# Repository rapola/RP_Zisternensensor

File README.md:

# RP_Zisternensensor
Wasser-Füllstandsensor für Zisternen
 * ## Hauptplatine für Auswertung und MQTT Sender
 
  <br>
  
  * ## Level Sensor:
  
  <br>

  ---
    
### Schematic

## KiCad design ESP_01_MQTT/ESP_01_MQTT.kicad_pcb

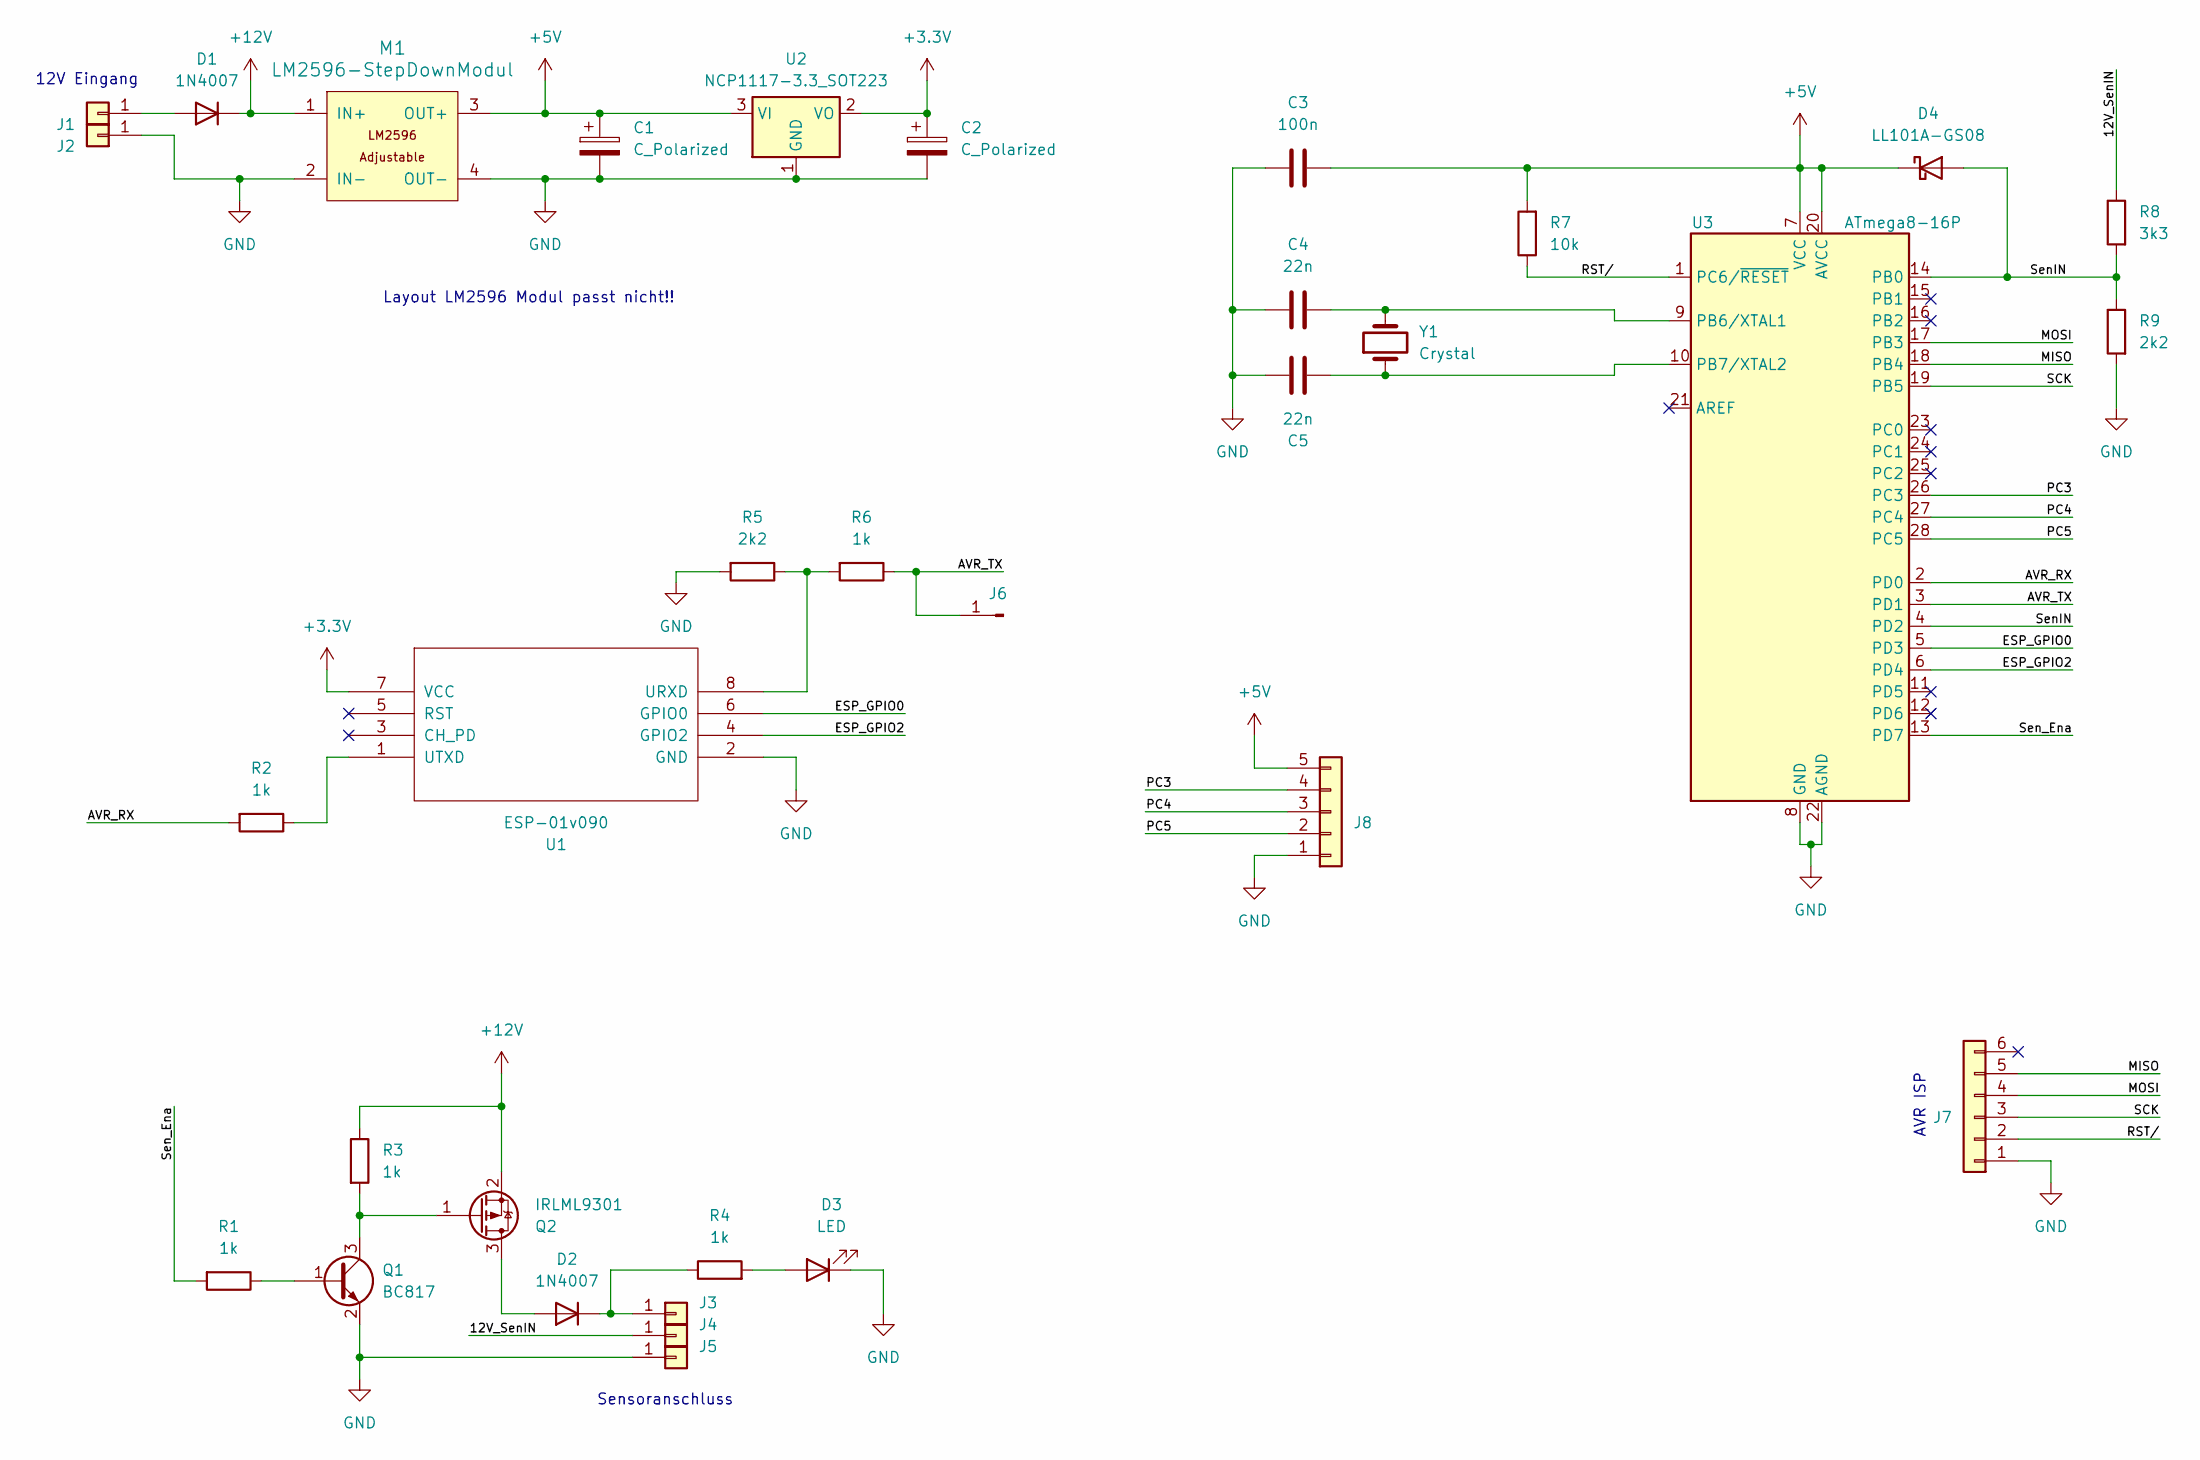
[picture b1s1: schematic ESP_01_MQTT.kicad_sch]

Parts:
C1, C2: C_Polarized; CP_Radial_D5.0mm_P2.00mm
C3: 100n; C_0805_2012Metric
C4, C5: 22n; C_0805_2012Metric
D1, D2: 1N4007; D_DO-41_SOD81_P10.16mm_Horizontal
D3: LED; LED_0805_2012Metric
D4: LL101A-GS08; D_MiniMELF
J1, J2, J3, J4, J5: Conn_01x01; Wago236-743_RM5
J6: Conn_01x01_Pin; PinHeader_1x01_P2.54mm_Vertical
J7: Conn_01x06; Molex_PicoBlade_53398-0671_1x06-1MP_P1.25mm_Vertical
J8: Conn_01x05; PinHeader_1x05_P2.54mm_Vertical
M1: LM2596-StepDownModul; YAAJ_DCDC_StepDown_LM2596_noSilk
Q1: BC817; SOT-23
Q2: IRLML9301; SOT-23
R1, R2, R3, R4, R6: 1k; R_0805_2012Metric
R5, R9: 2k2; R_0805_2012Metric
R7: 10k; R_0805_2012Metric
R8: 3k3; R_0805_2012Metric
U1: ESP-01v090; ESP-01
U2: NCP1117-3.3_SOT223; SOT-223-3_TabPin2
U3: ATmega8-16P; DIP-28_W7.62mm
Y1: Crystal; Crystal_HC49-4H_Vertical

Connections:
+3.3V: C2.1, U1.7 (VCC), U2.2 (VO)
+5V: C1.1, C3.2, D4.1 (K), J8.5, M1.3 (OUT+), R7.2, U2.3 (VI), U3.7 (VCC), U3.20 (AVCC)
+12V: D1.1 (K), M1.1 (IN+), Q2.2 (S), R3.1
/12V_SenIN: J4.1, R8.1
/AVR_RX: R2.2, U3.2 (PD0)
/AVR_TX: J6.1, R6.1, U3.3 (PD1)
/ESP_GPIO0: U1.6 (GPIO0), U3.5 (PD3)
/ESP_GPIO2: U1.4 (GPIO2), U3.6 (PD4)
/MISO: J7.5, U3.18 (PB4)
/MOSI: J7.4, U3.17 (PB3)
/PC3: J8.4, U3.26 (PC3)
/PC4: J8.3, U3.27 (PC4)
/PC5: J8.2, U3.28 (PC5)
/RST/: J7.2, R7.1, U3.1 (PC6/~RESET)
/SCK: J7.3, U3.19 (PB5)
/SenIN: D4.2 (A), R8.2, R9.1, U3.4 (PD2), U3.14 (PB0)
/Sen_Ena: R1.2, U3.13 (PD7)
GND: C1.2, C2.2, C3.1, C4.1, C5.1, D3.1 (K), J2.1, J5.1, J7.1, J8.1, M1.2 (IN-), M1.4 (OUT-), Q1.2 (E), R5.2, R9.2, U1.2 (GND), U2.1 (GND), U3.8 (GND), U3.22 (AGND)
unnamed: D1.2 (A), J1.1
unnamed: D2.2 (A), Q2.3 (D)
unnamed: D2.1 (K), J3.1, R4.1
unnamed: D3.2 (A), R4.2
unnamed: Q1.1 (B), R1.1
unnamed: Q1.3 (C), Q2.1 (G), R3.2
unnamed: R5.1, R6.2, U1.8 (URXD)
unnamed: R2.1, U1.1 (UTXD)
unnamed: C4.2, U3.9 (PB6/XTAL1), Y1.2
unnamed: C5.2, U3.10 (PB7/XTAL2), Y1.1

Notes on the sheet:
12V Eingang
Layout LM2596 Modul passt nicht!!
Sensoranschluss
AVR ISP

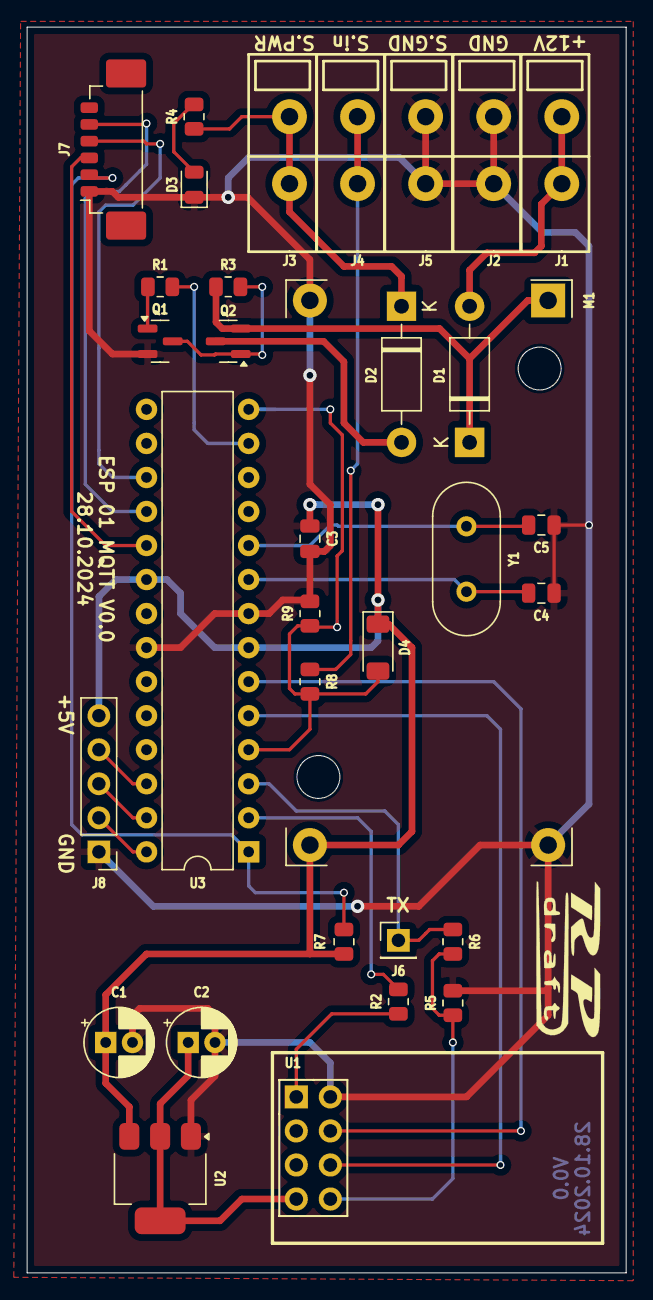
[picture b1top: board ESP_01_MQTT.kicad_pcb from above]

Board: 2 copper layers, 44.7 x 93.0 mm, 33 parts (0 on the bottom side), 28 nets.

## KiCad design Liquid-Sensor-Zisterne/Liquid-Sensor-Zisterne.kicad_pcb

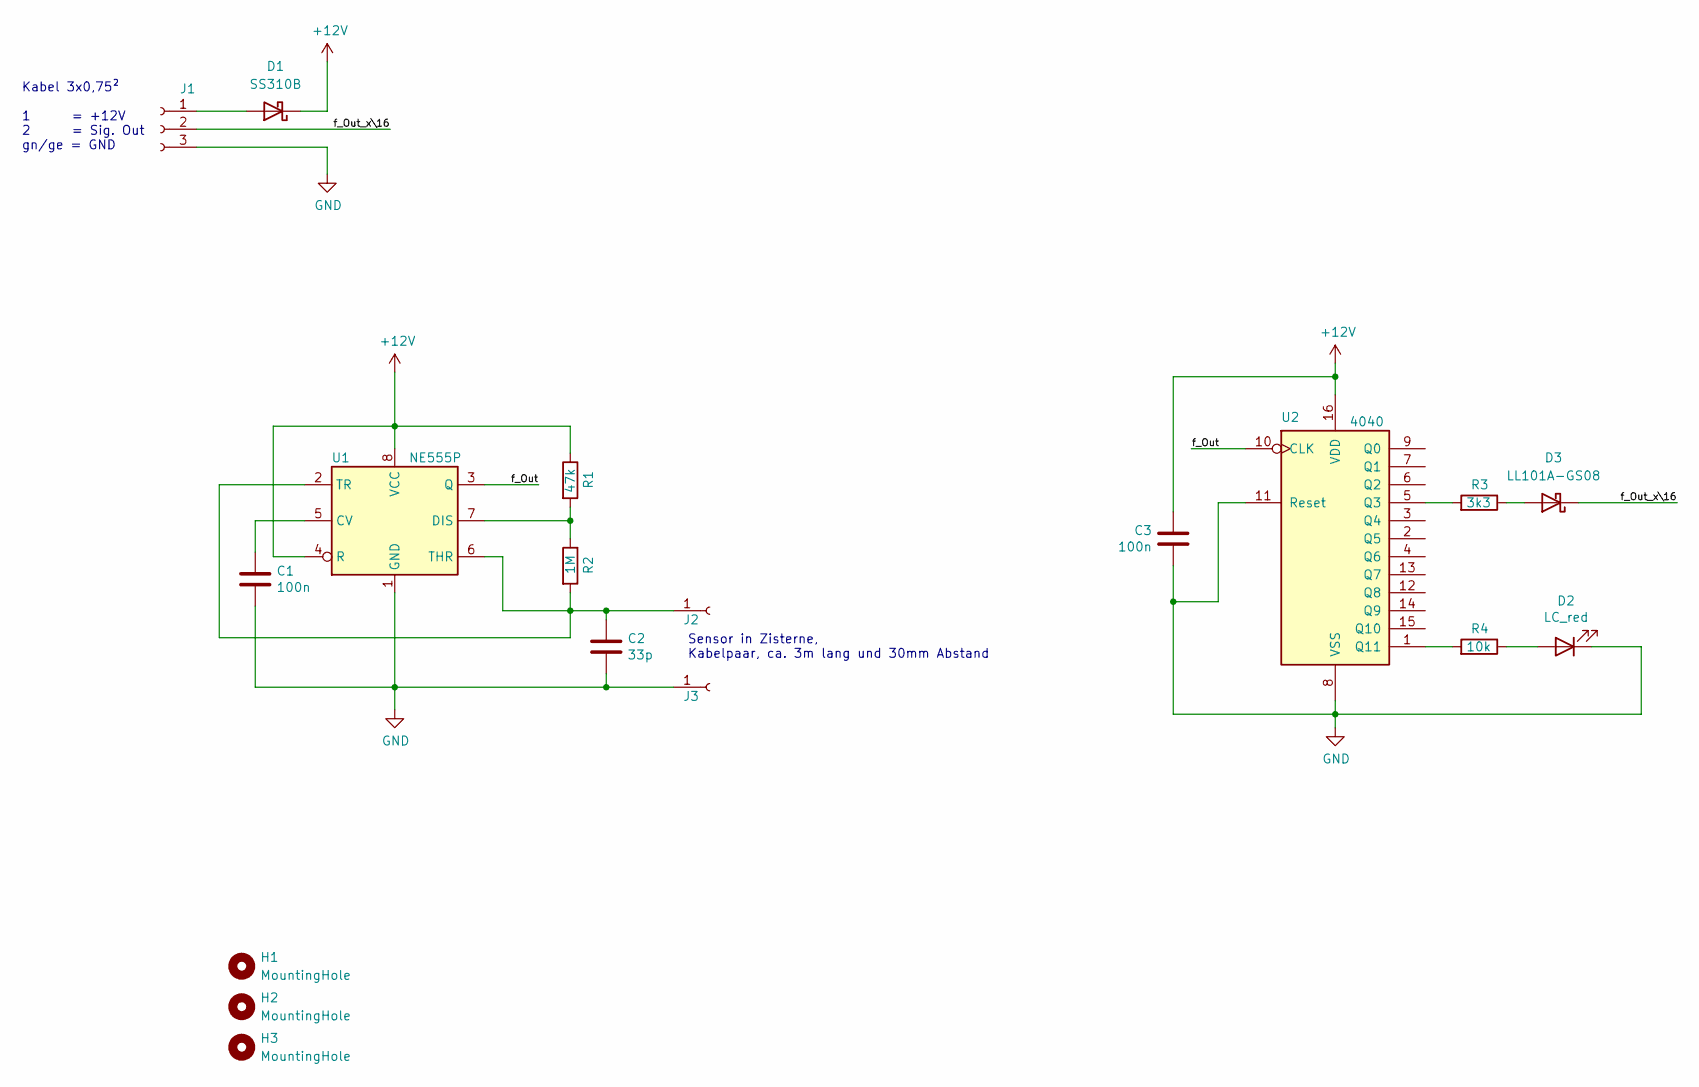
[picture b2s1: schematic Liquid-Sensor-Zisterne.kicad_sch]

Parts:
C1, C3: 100n; C_0805_2012Metric_Pad1.18x1.45mm_HandSolder
C2: 33p; C_Disc_D3.4mm_W2.1mm_P2.50mm
D1: SS310B; D_SMB_Handsoldering
D2: LC_red; LED_D3.0mm
D3: LL101A-GS08; D_MiniMELF
H1, H2, H3: MountingHole; MountingHole_3.2mm_M3_DIN965
J1: Conn_01x03_Female; PinHeader_1x03_P2.54mm_Horizontal
J2, J3: Conn_01x01_Female; TestPoint_Loop_D3.50mm_Drill1.4mm_Beaded
R1: 47k; R_0805_2012Metric_Pad1.20x1.40mm_HandSolder
R2: 1M; R_0805_2012Metric_Pad1.20x1.40mm_HandSolder
R3: 3k3; R_0805_2012Metric_Pad1.20x1.40mm_HandSolder
R4: 10k; R_0805_2012Metric_Pad1.20x1.40mm_HandSolder
U1: NE555P; SO-8_3.9x4.9mm_P1.27mm
U2: 4040; SOIC-16_3.9x9.9mm_P1.27mm

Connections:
+12V: C3.2, D1.1 (K), R1.1, U1.4 (R), U1.8 (VCC), U2.16 (VDD)
/f_Out: U1.3 (Q), U2.10 (CLK)
/f_Out_x\16: D3.1 (K), J1.2
GND: C1.2, C2.1, C3.1, D2.1 (K), J1.3, J3.1, U1.1 (GND), U2.8 (VSS), U2.11 (Reset)
unnamed: D1.2 (A), J1.1
unnamed: D2.2 (A), R4.1
unnamed: D3.2 (A), R3.1
unnamed: C2.2, J2.1, R2.2, U1.2 (TR), U1.6 (THR)
unnamed: C1.1, U1.5 (CV)
unnamed: R1.2, R2.1, U1.7 (DIS)
unnamed: R3.2, U2.5 (Q3)
unnamed: R4.2, U2.1 (Q11)

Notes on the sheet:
Sensor in Zisterne, Kabelpaar, ca. 3m lang und 30mm Abstand
Kabel 3x0,75² 1 = +12V 2 = Sig. Out gn/ge = GND

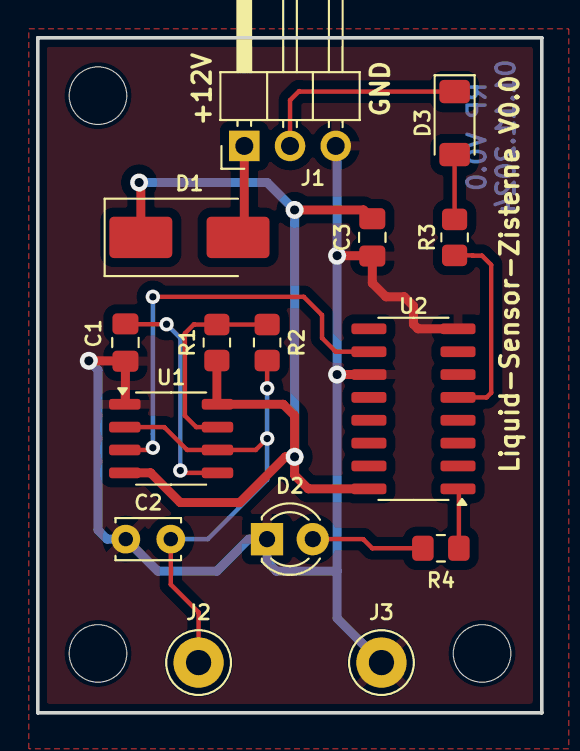
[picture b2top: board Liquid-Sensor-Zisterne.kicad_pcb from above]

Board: 2 copper layers, 28.0 x 37.5 mm, 18 parts (0 on the bottom side), 12 nets.

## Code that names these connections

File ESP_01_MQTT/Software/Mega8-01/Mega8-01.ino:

/*
Auswertung Freqeunzeingang
Arduino 1.8.19

AtMega8
PB0  AVR_ICP1          input from level-sensor
PD7  AVR_ENA_Sen12V    output, switch level-sensor on/off

- corresponding software: "ESP8266", always use same Vx.x !!
ToDo

*/

#include "src/RP_Arduino-SerialCommand/SerialCommand.h"	  		//Serial Command
#include <avr/interrupt.h> 

//-------------------------------------------------------
//global variables / constants
char SW_Vers[] = "Mega8-V1.0";

const uint8_t AVR_ICP1        = 8;                            //PB0;
const uint8_t AVR_ENA_Sen12V  = 7;                            //PD7;
const uint8_t PC_3            = 17;                           //not used, input pullup
const uint8_t PC_4            = 18;                           //not used, input pullup
const uint8_t PC_5            = 19;                           //not used, input pullup

const uint8_t AVR_ENA_Serial  = 3;                            //PD3; GPIO0 from ESP


struct tm{
  uint16_t capture_val;
  uint16_t ovf_val;
  uint16_t curr_capt_val;
  uint16_t curr_ovf_val;
};

volatile tm ICP;
uint32_t freq_timeout = 3000;                                 //3s timeout
uint8_t get_freq = 0;                                         //get ICP-val state machine
uint8_t rst_timeout = 0;                                      //for check if timeout has happend

//---------------------------------------------------------------------
// create serial command object
SerialCommand sdata;

//####################################################################
//--------------------------------------------------------------------
void setup() {
  delay(1000);
  Serial.begin(115200);
  //---------------------------------------------------------------------
  // setup callbacks for serial commands
  sdata.addCommand("#SW", SEND_SWVERSION);          			    //send software version
  sdata.addCommand("GETF", GET_FREQ);                         //set bit for getting and then sending ICP1_cnt
  sdata.setDefaultHandler(unrecognized);            			    //handling of not matching commands, send what?
  //Serial.printf("Software Version: %s \r\n", SW_Vers);
 
 //-------------------------------------------------------
  // Pins
  pinMode(AVR_ICP1, INPUT);
  pinMode(AVR_ENA_Serial, INPUT);
  pinMode(AVR_ENA_Sen12V, OUTPUT);
  pinMode(PC_3, INPUT_PULLUP);
  pinMode(PC_4, INPUT_PULLUP);
  pinMode(PC_5, INPUT_PULLUP);

  while(digitalRead(AVR_ENA_Serial) == HIGH){
    __asm__("nop\n\t");                                       //Do nothing
  }

 //-------------------------------------------------------
 // Timer
  noInterrupts();                                           //Timer 1 on, input capture Pin PB0 = ICP1 = 8
  TCCR1A = 0;
  TCCR1B = 0;
  TCCR1B |= (1 << ICNC1) | (1 << ICES1) | (1 << CS10);      //noise cancel, rising edge, clock/8
  //TIMSK1  |= (1 << ICIE1) | (1 << TOIE1);                   //Mega 328 input capture interrupt, overflow interrupt
  TIMSK  |= (1 << TICIE1) | (1 << TOIE1);                   //Mega 8 input capture interrupt, overflow interrupt
  interrupts();
  
}

//####################################################################
//--------------------------------------------------------------------
void loop() {
  //call frequently to handle serial data communication
  sdata.readSerial(); 

  if(get_freq == 1){
    digitalWrite(AVR_ENA_Sen12V, HIGH);                       //switch sensor on
    get_freq = 2;
    delay(2000);                                               //wait 300mS...
    rst_timeout = 1;
  }
  if(get_freq == 0){
    digitalWrite(AVR_ENA_Sen12V, LOW);                       //switch sensor off
  }
  
static uint32_t ms_start_measure;
if(get_freq == 2){
    ms_start_measure = millis();                              //timeout
    get_freq = 0;                                             //only once

    while((millis() - ms_start_measure) < freq_timeout){
      if(rst_timeout == 0){
        break;
      }
    }
 
    if(rst_timeout == 0){
      Serial.printf("ICP1val: %u %u\r\n", ICP.ovf_val, ICP.capture_val);
    }
    else{
      Serial.printf("ICP1err: Timeout\r\n");
    }
  }

}

//####################################################################
//--------------------------------------------------------------------
//TIM1 OVF 
ISR(TIMER1_OVF_vect){
  if(ICP.curr_ovf_val < 0xFFFF){
    ICP.curr_ovf_val ++;                                          // count overflows
  }
}

//-------------------------------------------------------
//TIM1 CAPT 
ISR(TIMER1_CAPT_vect){
  TCNT1 = TCNT1 - ICR1;                                       //new timer init, TimerCounter - inputCapture 
  ICP.curr_capt_val = ICR1;
  ICP.ovf_val = ICP.curr_ovf_val;
  ICP.capture_val = ICP.curr_capt_val;
  ICP.curr_ovf_val = 0;
  rst_timeout = 0;

}

//####################################################################
//--------------------------------------------------------------------
//send software version
void SEND_SWVERSION() {
  Serial.printf("SW_Vers: %s \r\n", SW_Vers);
}

//--------------------------------------------------------------------
//set bit for getting ICP1_cnt
void GET_FREQ(){
  get_freq = 1;
  //Serial.printf("Get_freq = %i \r\n", get_freq); 
}

//-------------------------------------------------------------------
// non usable data received
void unrecognized(const char *command) {
  //Serial.printf("What? \r\n");                              //Debug only
  __asm__("nop\n\t");                                         //Do nothing
}

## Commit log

2024-11-01 Projekt zusammengefasst
2024-11-01 Serial_command added
2024-11-01 added pics
2024-11-01 updated pics
2024-11-01 further project organisation
2024-11-01 added Abstandshalter
2024-11-03 Platine bestellt
2024-11-03 Kosmetic
2024-11-04 further programming
2024-11-07 Hardware gelötet
2024-11-11 further sofware testing
2024-11-12 Final Releas Mega8-V1.0 and ESP8266-V1.0
2024-11-24 Alle Teile fertig, kurz vor Einbau
2025-05-26 Changed SSID in code
2025-06-11 reconnect loop
    System hang. no mqtt response, webserver was working. added reconnect loop
